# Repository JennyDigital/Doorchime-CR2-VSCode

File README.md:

# I Now Have a Website for this Project!

[https://jennys-stm32-dsp-audio-engine.netlify.app/](https://jennys-stm32-dsp-audio-engine.netlify.app/)

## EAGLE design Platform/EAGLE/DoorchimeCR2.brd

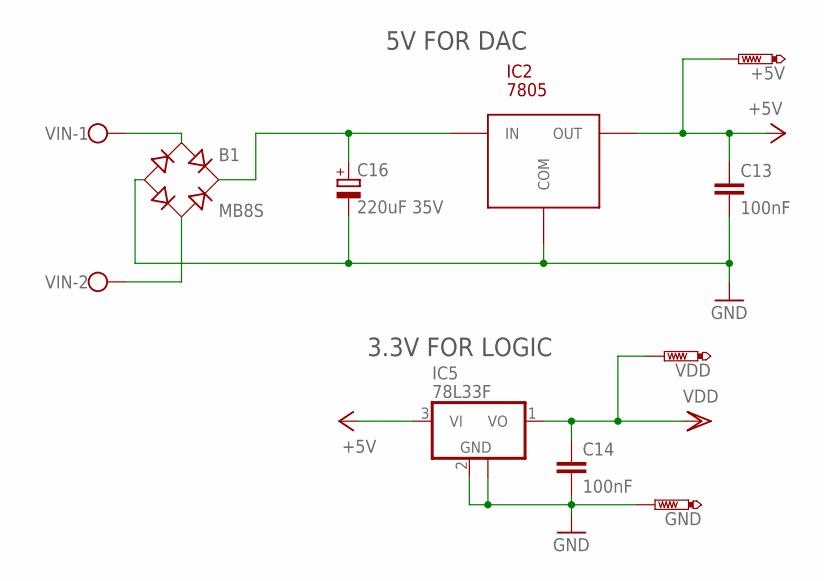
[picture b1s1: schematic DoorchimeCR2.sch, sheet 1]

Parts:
+5V: PTR1TP15R; TP15R
B1: MB8S; SOIC-4
C13, C14: 100nF; C0603
C16: 220uF 35V; 153CLV-0807
GND: PTR1TP15R; TP15R
IC2: 7805; D2PAK
IC5: 78L33F; SOT89
VDD: PTR1TP15R; TP15R
VIN: W237-102

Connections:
+5V: +5V.TP, C13.1, IC2.OUT, IC5.3 (VI); also elsewhere on the board
GND: B1.-, C13.2, C14.2, C16.-, GND.TP, IC2.COM, IC5.2 (GND), IC5.2@1 (GND); also elsewhere on the board
VDD: C14.1, IC5.1 (VO), VDD.TP; also elsewhere on the board
VIN1: B1.~1 (AC1), VIN.1
VIN2: B1.~2 (AC2), VIN.2
VIN+: B1.+, C16.+, IC2.IN

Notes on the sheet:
5V FOR DAC
3.3V FOR LOGIC

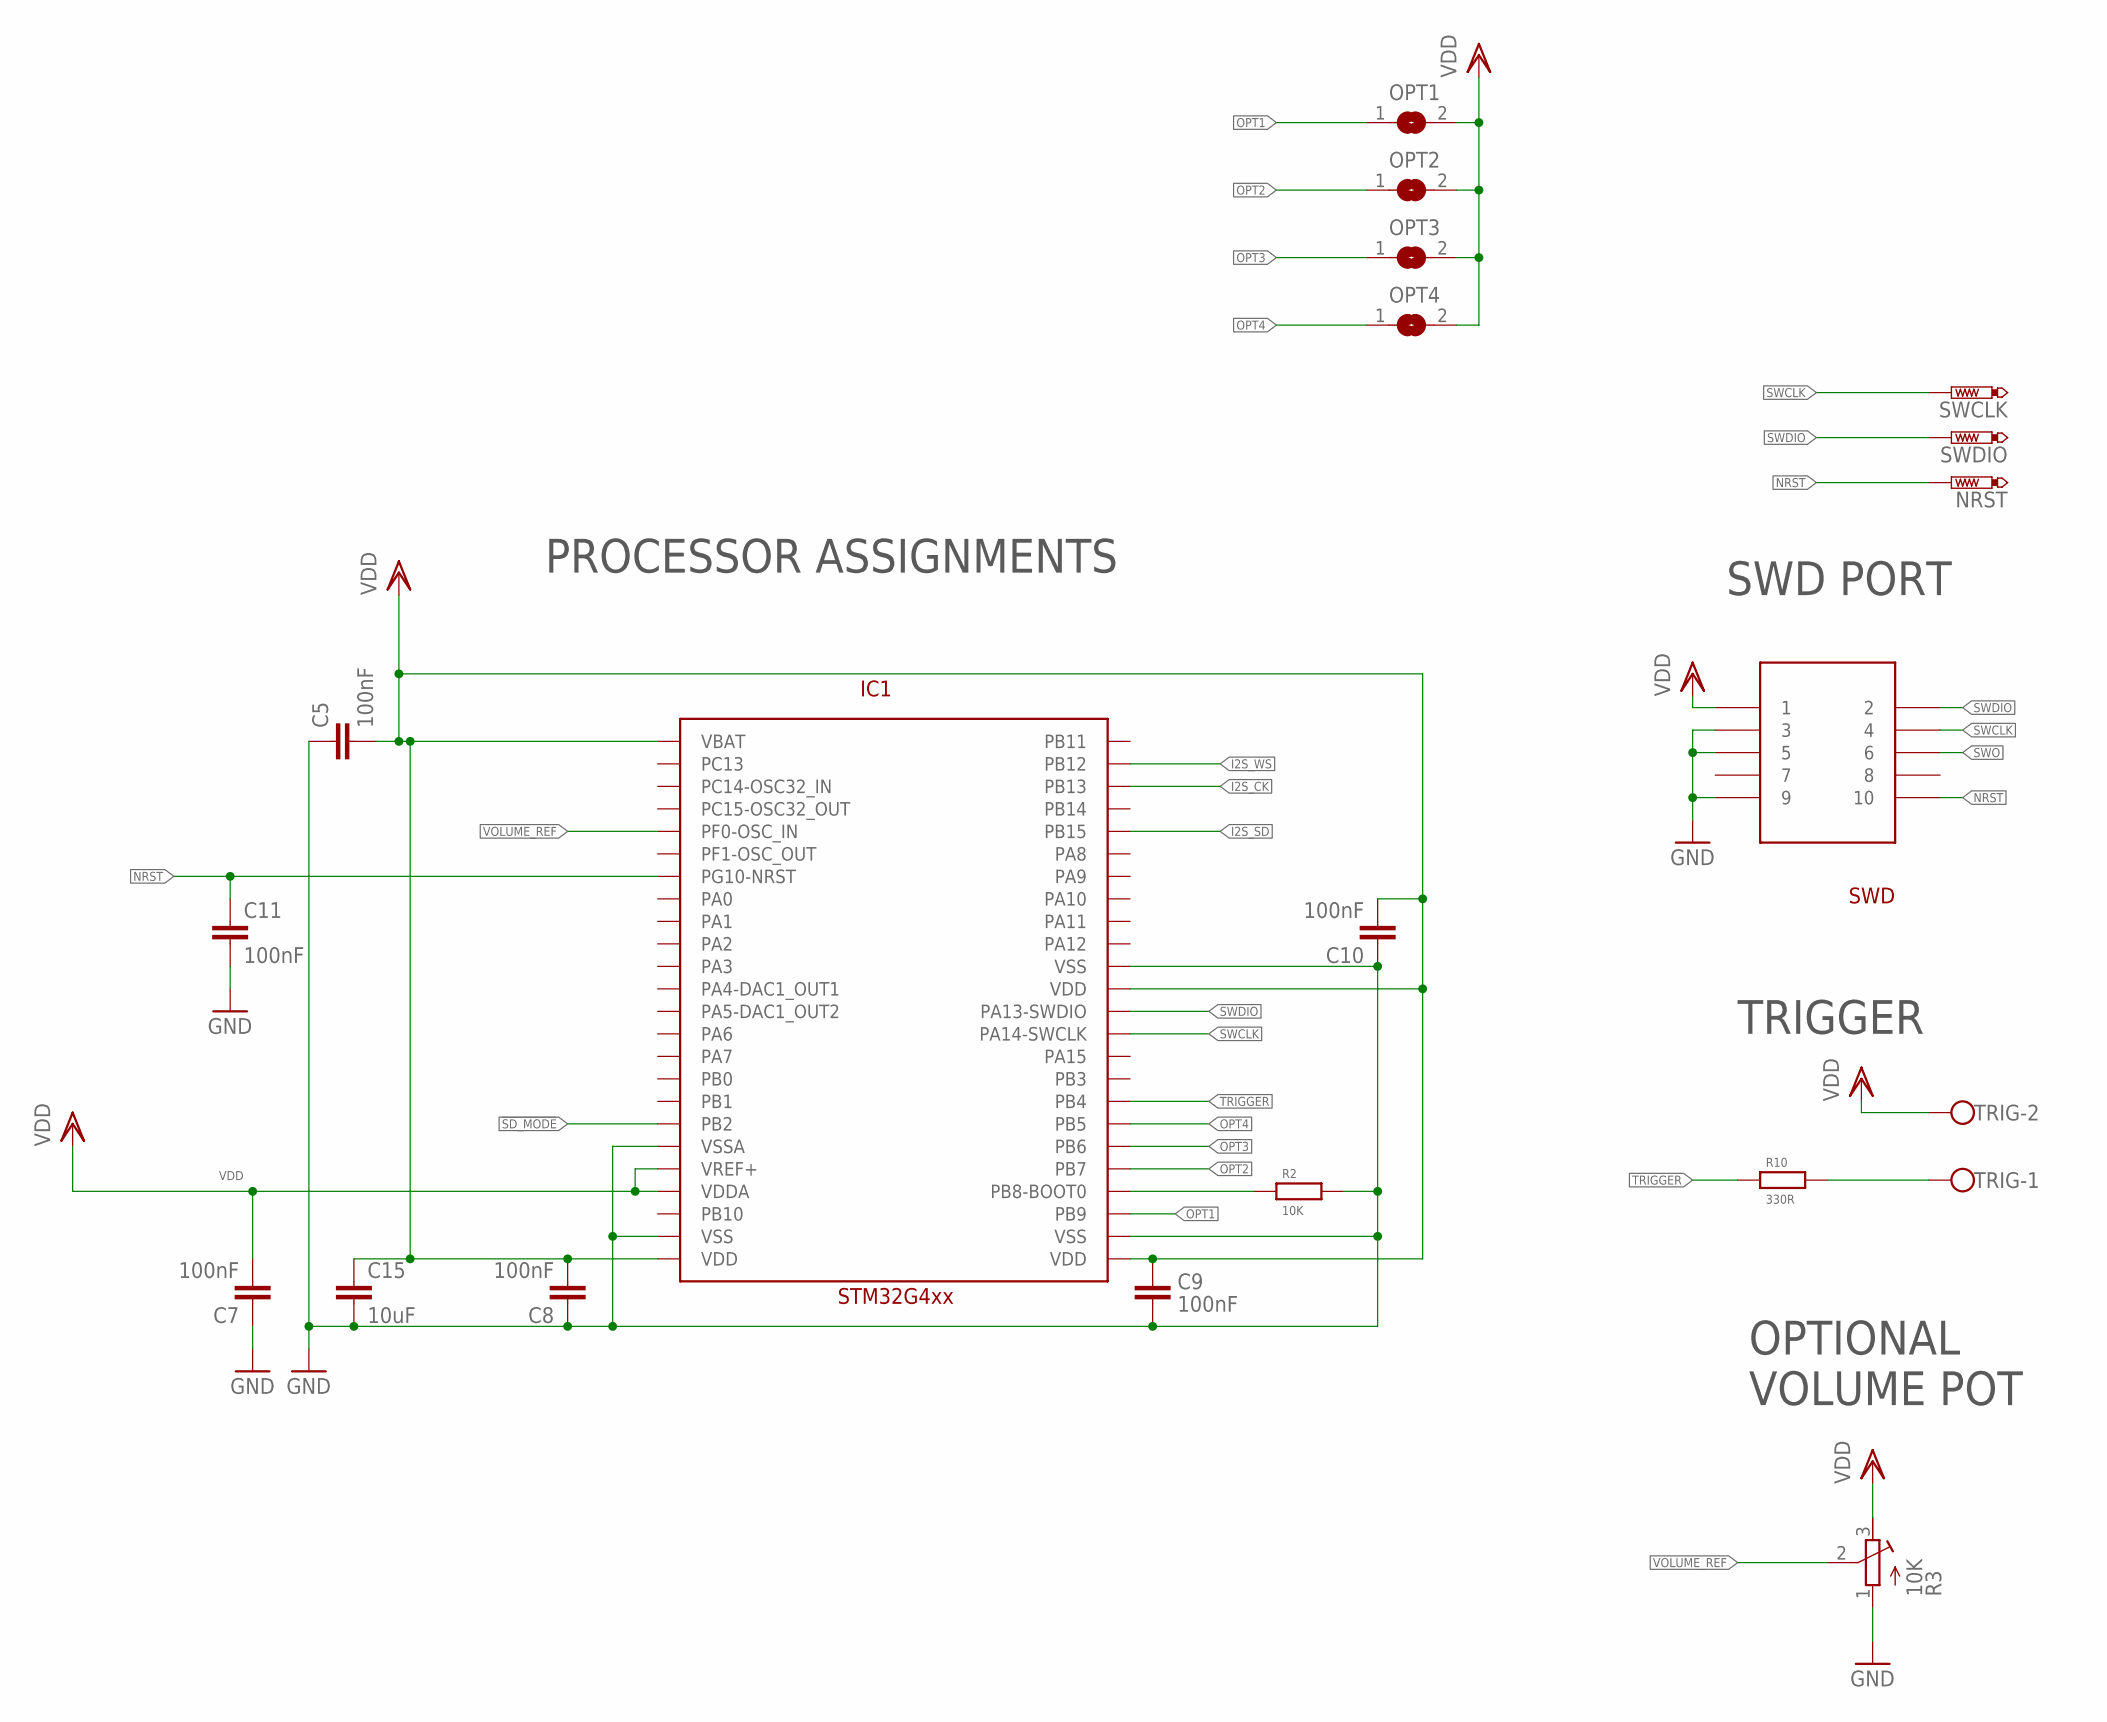
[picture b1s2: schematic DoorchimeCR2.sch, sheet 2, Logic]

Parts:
C5, C7, C8, C9, C10, C11: 100nF; C0603
C15: 10uF; C0603
IC1: STM32G4xx; TQFP48
NRST: PTR1TP15R; TP15R
OPT1, OPT2, OPT3, OPT4: SJ
R2: 10K; R0603
R3: 10K; RTRIM3339P
R10: 330R; R0603
SWCLK: PTR1TP15R; TP15R
SWD: FTSH-105-01; FTSH-105-01-XXX-DV-K
SWDIO: PTR1TP15R; TP15R
TRIG: W237-102

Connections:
!SD_MODE: IC1.PB2; also elsewhere on the board
BOOT0: IC1.PB8-BOOT0, R2.1
GND: C5.1, C7.1, C8.1, C9.1, C10.1, C11.2, C15.2, IC1.VSS@23 (VSS), IC1.VSS@35 (VSS), IC1.VSS@47 (VSS), IC1.VSSA, R2.2, R3.1 (E), SWD.3, SWD.5, SWD.9; also elsewhere on the board
I2S_CK: IC1.PB13; also elsewhere on the board
I2S_SD: IC1.PB15; also elsewhere on the board
I2S_WS: IC1.PB12; also elsewhere on the board
NRST: C11.1, IC1.PG10-NRST, NRST.TP, SWD.10
OPT1: IC1.PB9, OPT1.1
OPT2: IC1.PB7, OPT2.1
OPT3: IC1.PB6, OPT3.1
OPT4: IC1.PB5, OPT4.1
SWCLK: IC1.PA14-SWCLK, SWCLK.TP, SWD.4
SWDIO: IC1.PA13-SWDIO, SWD.2, SWDIO.TP
SWO: SWD.6
TRIG1: R10.2, TRIG.1
TRIGGER: IC1.PB4, R10.1
VDD: C5.2, C7.2, C8.2, C9.2, C10.2, C15.1, IC1.VBAT, IC1.VDD@24 (VDD), IC1.VDD@36 (VDD), IC1.VDD@48 (VDD), IC1.VDDA, IC1.VREF+, OPT1.2, OPT2.2, OPT3.2, OPT4.2, R3.3 (A), SWD.1, TRIG.2; also elsewhere on the board
VOLUME_REF: IC1.PF0-OSC_IN, R3.2 (S)

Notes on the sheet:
PROCESSOR ASSIGNMENTS
TRIGGER
SWD PORT
OPTIONAL VOLUME POT

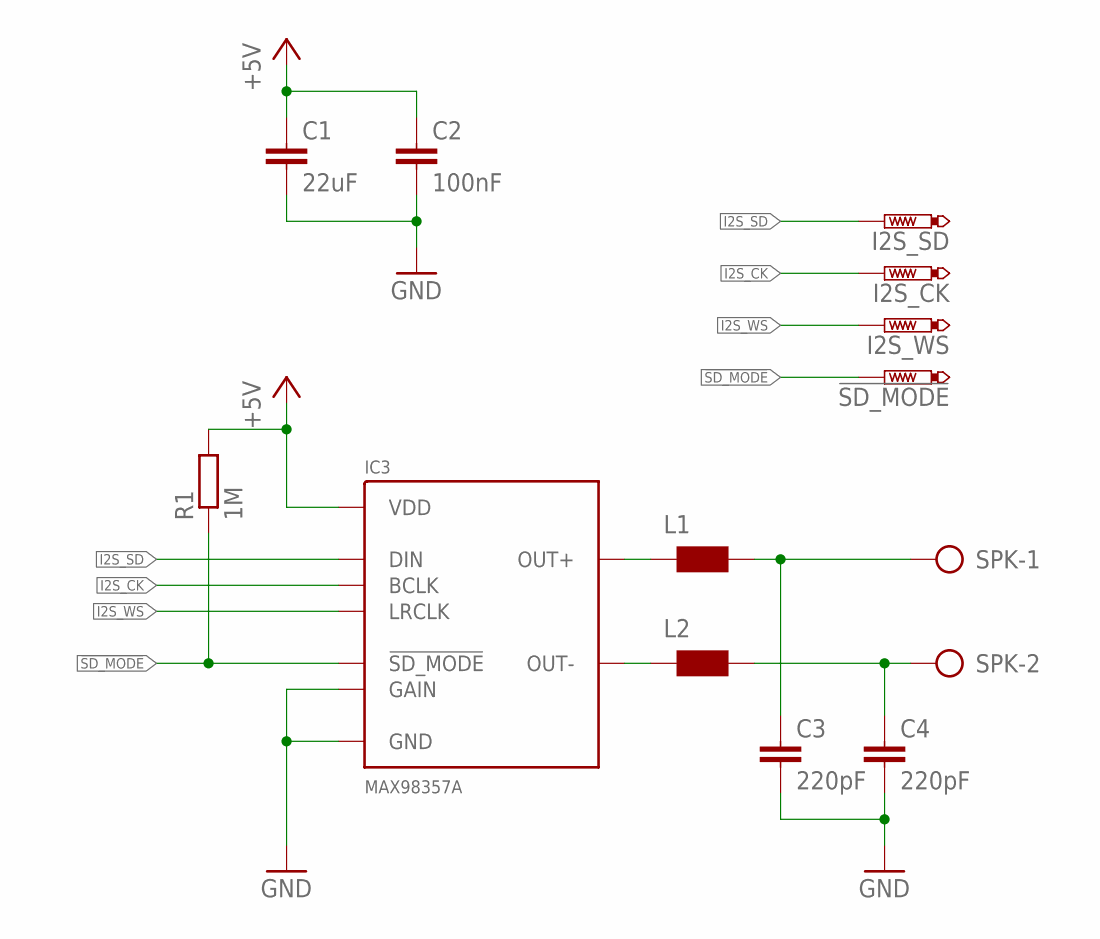
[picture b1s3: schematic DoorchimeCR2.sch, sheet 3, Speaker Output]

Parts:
!SD_MODE: PTR1TP15R; TP15R
C1: 22uF; C0603
C2: 100nF; C0603
C3, C4: 220pF; C0603
I2S_CK, I2S_SD, I2S_WS: PTR1TP15R; TP15R
IC3: MAX98357A; TQFN-16
L1, L2: WE-CBF_0603; 0603
R1: 1M; R0603
SPK: W237-102

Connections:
!SD_MODE: !SD_MODE.TP, IC3.P$4 (!SD_MODE), R1.1; also elsewhere on the board
+5V: C1.1, C2.1, IC3.P$7 (VDD), IC3.P$8 (VDD), R1.2; also elsewhere on the board
GND: C1.2, C2.2, C3.2, C4.2, IC3.P$2 (GAIN), IC3.P$3 (GND), IC3.P$11 (GND), IC3.P$15 (GND), IC3.P$EP (GND); also elsewhere on the board
I2S_CK: I2S_CK.TP, IC3.P$16 (BCLK); also elsewhere on the board
I2S_SD: I2S_SD.TP, IC3.P$1 (DIN); also elsewhere on the board
I2S_WS: I2S_WS.TP, IC3.P$14 (LRCLK); also elsewhere on the board
unnamed: IC3.P$9 (OUT+), L1.1
unnamed: IC3.P$10 (OUT-), L2.1
unnamed: C4.1, L2.2, SPK.2
unnamed: C3.1, L1.2, SPK.1

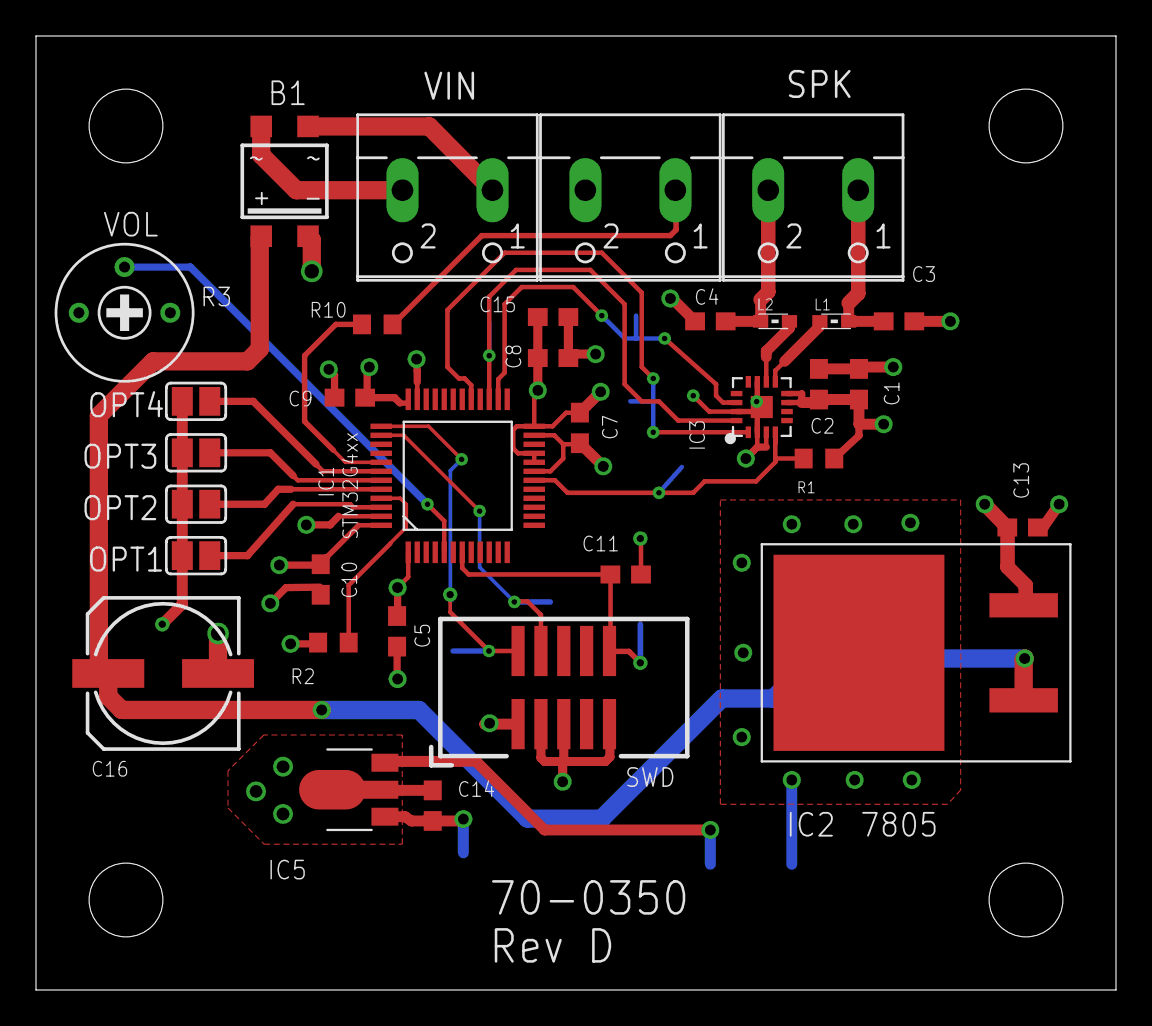
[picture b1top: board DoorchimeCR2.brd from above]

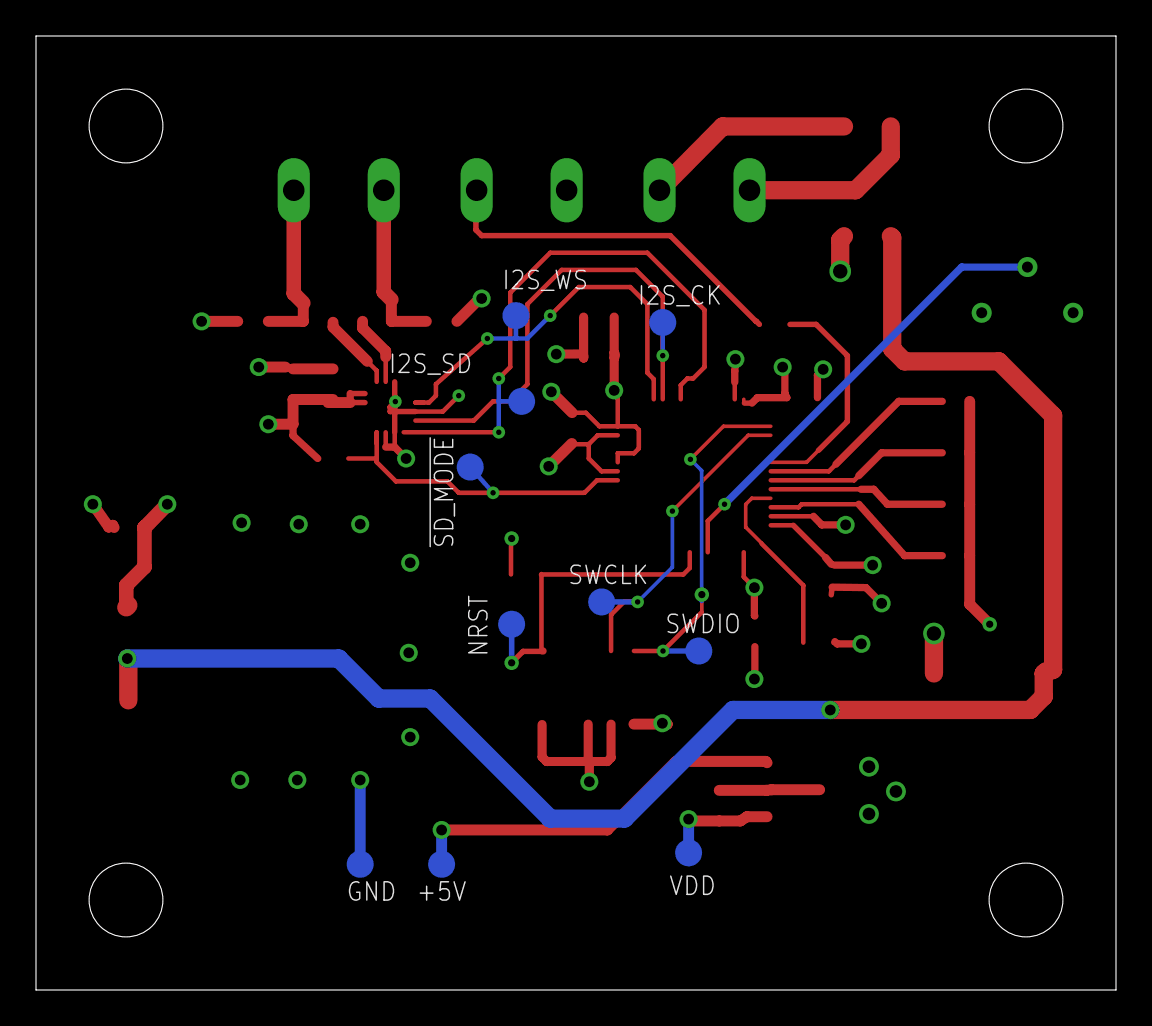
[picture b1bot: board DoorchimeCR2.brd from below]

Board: 4 copper layers, 60.0 x 53.0 mm, 43 parts (10 on the bottom side), 25 nets.

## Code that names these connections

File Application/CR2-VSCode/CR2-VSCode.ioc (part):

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Mcu.Name=STM32G474C(B-C-E)Tx
Mcu.Package=LQFP48
Mcu.UserName=STM32G474CETx
PA13.Mode=Serial_Wire
PA13.Signal=SYS_JTMS-SWDIO
PA14.Mode=Serial_Wire
PA14.Signal=SYS_JTCK-SWCLK
PB12.GPIOParameters=GPIO_Speed
PB12.GPIO_Speed=GPIO_SPEED_FREQ_MEDIUM
PB12.Mode=Half_Duplex_Master
PB12.Signal=I2S2_WS
PB13.GPIOParameters=GPIO_Speed
PB13.GPIO_Speed=GPIO_SPEED_FREQ_MEDIUM
PB13.Mode=Half_Duplex_Master
PB13.Signal=I2S2_CK
PB15.GPIOParameters=GPIO_Speed
PB15.GPIO_Speed=GPIO_SPEED_FREQ_MEDIUM
PB15.Mode=Half_Duplex_Master
PB15.Signal=I2S2_SD
PB2.GPIOParameters=GPIO_PuPd,GPIO_Label,GPIO_ModeDefaultOutputPP
PB2.GPIO_Label=NSD_MODE
PB2.GPIO_ModeDefaultOutputPP=GPIO_MODE_OUTPUT_OD
PB2.GPIO_PuPd=GPIO_NOPULL
PB2.Signal=GPIO_Output
PB4.GPIOParameters=GPIO_PuPd,GPIO_Label
PB4.GPIO_Label=TRIGGER
PB4.GPIO_PuPd=GPIO_PULLDOWN
PB4.Signal=GPIO_Input
PB5.GPIOParameters=GPIO_PuPd,GPIO_Label
PB5.GPIO_Label=OPT4
PB5.GPIO_PuPd=GPIO_PULLDOWN
PB5.Signal=GPIO_Input
PB6.GPIOParameters=GPIO_PuPd,GPIO_Label
PB6.GPIO_Label=OPT3
PB6.GPIO_PuPd=GPIO_PULLDOWN
PB6.Signal=GPIO_Input
PB7.GPIOParameters=GPIO_PuPd,GPIO_Label
PB7.GPIO_Label=OPT2
PB7.GPIO_PuPd=GPIO_PULLDOWN
PB7.Signal=GPIO_Input
PB9.GPIOParameters=GPIO_PuPd,GPIO_Label
PB9.GPIO_Label=OPT1
PB9.GPIO_PuPd=GPIO_PULLDOWN
PB9.Signal=GPIO_Input
RCC.HSE_VALUE=8000000
RCC.SYSCLKFreq_VALUE=96000000
RCC.SYSCLKSource=RCC_SYSCLKSOURCE_PLLCLK
board=custom

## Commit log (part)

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2025-12-20 Added all project files
2025-12-21 Tidied up comments FIX: Fixed a bug in the volume control I'd accidentally introducedd
2025-12-22 Just a aesthetic update
2025-12-24 Added some nice new sounds
2025-12-27 doorchime now killbill11k
2026-01-17 FIXUP: Change error handling to shutdown handling in audio playback TIDYUP: Remove redundant null pointer checks in audio chunk copying functions TIDYUP: Restructure code for better readability in au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
2026-01-19 fixup: adjust end-of-sample checks for pointer types in audio playback code fixup: removed unneccesary commented out code in main.c fixup: removed inappropriate pb_state assignment in TX complete cal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
2026-01-19 FIX: Graceful handling of end-of-sample in audio playback FIX: Corrected typo in volume reading function comment
2026-01-20 FEATURE: Enable EXTI interrupt callbacks and save power by entering sleep mode.
2026-01-21 Improved trigger handling with timout to sleep mode.
2026-01-22 Added a new sound dalby_tritone16b16
2026-01-22 Still working to find a non-popping way to stop playback.
2026-01-23 Added fade-out functionality to audio playback to prevent popping sound at the end of playback. Implemented a function to shut down audio playback gracefully. Adjusted system clock configuration for 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
2026-01-23 FEATURE: Implement a DC blocking filter to remove DC offset from audio samples, improving sound quality.
2026-01-23 Minor tweak to improve code readability in main.c
2026-01-23 FIXED: Added back HAL_I2S_DMAStop call in
2026-01-23 FIX: Fade effect not working properly in certain conditions
2026-01-24 Moved the filter chain to it's own function for clarity. Removed the need for a cast when calling PlaySample by changing the parameter type.
2026-01-24 Added tasks
2026-01-24 Somewhere, I have no recollection, Code appeared in MX_GPIO_Init function that broke the build. It's been removed.
2026-01-24 Build system changes to improve compile times and add new toolchain support.
2026-01-24 Modularity Improvements to Audio Engine
2026-01-24 Adjusted volume reading logic so that we only call the ReadVolume function once per buffer fill, improving efficiency and readability.
2026-01-24 Altered the cutoff frequencies of the low-pass filters for 16-bit audio samples by changing the alpha coefficients in the audio_engine.h file. Updated the visualize_filters_enhanced.py script to refl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
2026-01-24 Add manual for audio_engine.h and generate filter report PDF script Remove AudioEngine_Init declaration from audio_engine.h
2026-01-25 Updated documentation and enhanced filter settings for improved audio quality. Updated graphs to reflect new filter configurations.
2026-01-25 FIX: Warmup documentation and adjust LPF levels
2026-01-25 Added a very nice pdf manual.
2026-01-25 Air lifting and brightening effect added to audio engine. Documentation updated accordingly. Added a new sound header and raw file for testing.
2026-01-25 Updated AUDIO_ENGINE_MANUAL.md and Audio_Engine_Manual.pdf to reflect changes to air effect filter gain and presets.
2026-01-25 Updates to REAME.md.
2026-01-25 Restructured documentation to live in Docs.
2026-01-26 FIXED: Pause and resume playback now fades out and in smoothly. FEATURE: Added functions to set and get fade times for fade-in, fade-out, and pause fade.
2026-01-26 Consolidated dma buffer handling for clearer code and improved memory usage.
2026-01-27 Updated documentation and increased biquad filter performance in audio engine.
2026-01-28 Added calculated delay for shutdown sequence to complete before stopping audio playback.
2026-01-28 Added firm low-pass filter option to PlaySample function call.
2026-01-28 Addeed further MIT Liccense header to main.c
2026-01-30 Uodated project to include latest HAL drivers and configurations. Added support for TIMER and ADC peripherals.
2026-01-30 Quick amendment to the order or restarting the ADC and TIM7 after waking from sleep mode.
2026-01-30 Fixed audio distortion issue in audio_engine.c
2026-01-30 Moved ShutDownAudio declaration to audio_engine.h and audio_engine.c
2026-01-31 Final aesthetic adjustments made to code style.
2026-01-31 Improved low-pass filter function and added soft noise gate in audio engine.
2026-01-31 Feature: Added getters and setters for audio engine configuration. There are still some to more to add.
2026-01-31 Moved some functions in static for reducing scope.
2026-02-01 FIX: Volume Input and Trigger Optimization NEW SOUND HEADER: We have a dalby_tritoneJan26 sound header and raw file added.
2026-02-01 Updated the audio emgine documentation and main header file.
2026-02-01 Added null check before using audio engine pointer. Updated BUG_REPORT.md to reflect changes in audio engine handling.
2026-02-02 FEATURE: PausePlayback is now non-blocking FIX: Removed DAC de and reinitialization during pause and resume to remove audio glitches
2026-02-03 Special configuration for Dalby Engineering offering.
2026-02-03 Update documentation and add interrupt protection utilities
    - Document pause/resume edge case handling (fade-in and end-of-file fadeout interruptions)
    - Update default pause fadeout duration (1.0 seconds instead of 100 ms)
    - Create interrupt_utils.h with ATOMIC_ENTER/ATOMIC_EXIT macros for atomic operations
    - Convert all spellings to British English (artifact -> artefact)
    - Update main.c to use new atomic operation macros
    - Document proportional scaling and quadratic fade curves in API reference
2026-02-03 Update filter report Air Effect presets to +1/+2/+3 dB
    - Correct presets list and summary text to reflect +1, +2, +3 dB options
    - Regenerate PDF with updated specifications
2026-02-03 Regenerated the manual
2026-02-03 Further fixes to AUDIO_ENGINE_FLOWCHART.md
2026-02-03 Hopefully the last fixes to AUDIO_ENGINE_FLOWCHART.md
2026-02-03 FIX: Added data and instruction barriers in interrupt utils.h to ensure proper ordering of operations when enabling and disabling interrupts.
2026-02-04 Improved volume reading and response handling. We now use a 16-bit volume range derived from a 12-bit ADC input, ensuring finer control over volume levels. The volume response can be toggled between 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
2026-02-04 FIX: Removed redundant GetStopStatus() function and replaced with GetPlaybackState().
2026-02-05 FEATURE: Added weak callback for end of sample playback.
2026-02-05 Improved contrast in the flowcharts.
2026-02-06 Added macro to fill audio buffer with midpoint value for silence, and used it in two places in audio_engine.c where the buffer needs to be filled with silence.
2026-02-06 We now fill the whole buffer with midpoint values when ending, this is because sometimes we end up playing a half chunk of audio after the fadeout has completed, which results in a small amount of no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
2026-02-06 Moved documentation to a better location.
2026-02-07 REFACTOR: Moved the macros STOP_IMMEDIATE and END_PLAYBACK_CLEANUP tO audio_engine.c as inline functions. This change was made to improve code maintainablilith and ease debugging.
2026-02-07 Moved helper functions RecalculateFadeSamples, EndPlaybackCleanup and StopImmediate to near the DMA callback function they're used in.
2026-02-07 FIX: ShutDownAudio now immediately halts DMA and resets state, instead of waiting for the buffer to drain. This is because StopPlayback does this asynchronously, and wse don't need two functions that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
2026-02-07 Updated pb8, pb16, pb8_end and pb16_end pointer names to end in _ptr for consistency and clarity.
2026-02-07 Updated documentation to reflect changes in audio engine API and fix inconsistencies.
2026-02-07 Removed mention of the non-existent CHANGELOG.md file.
2026-02-07 Minor corrections to documentation and code comments.
2026-02-07 Aesthetic changes to the code for better readability. No functional changes were made.
2026-02-07 Slighgt code tidying and refactoring for better readability and maintainability. No functional changes intended.
2026-02-08 Docuementation updates and license addition
2026-02-08 Removed #include's from main.c for files that have been deleted.
2026-02-09 FEATURE:- Added some new sound headers. FEATURE:- Added master enable flags for entire filter chains in audio_engine.c and audio_engine.h. FEATURE:- Updated main.c to set default states for new filte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
2026-02-11 CLEANUP: Removed redundant typedef and minor adjujstment to formatting.
2026-02-15 FIX:- Removed redundant code in audio_engine.c
2026-02-20 FIX: Double bounds check removed from ApplyLowPassFilter16Bit() in audio_engine.c Minimum volume clamp now defined by VOLUME_MIN_CLAMP in main.h.
2026-02-21 NEW SOUND: didgeridoo
2026-02-28 pb_state variable was changed from uint8_t to PB_StatusTypeDef enum for better readability and type safety. The GetPlaybackState and SetPlaybackState functions were updated accordingly to use the new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
2026-03-01 FIX: Cleaned up pause/resume logic and added comments. Edge case handling for invalid state transitions. Updated main.c to demonstrate pause/resume functionality with appropriate delays.
2026-03-01 Volume is now processed per frame rather than per chunk, which allows for more accurate volume control and better performance. Additionally, the audio engine now supports dynamic volume changes, allo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
2026-03-08 FIX: Ensure DAC is switched off after playback ends if power control is enabled, there were edge cases where it remained on after playback ended, this change adds a check to ensure it is switched off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
2026-03-08 Added a nice logo and updated the documentation. Portability guide and some minor code tweaks to prevent integer overflow in the biquad filter when processing 16-bit samples with certain configuratio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
2026-03-08 Update: links now updated.
2026-03-08 FIX: Markdown should now be rendered correctly on the website. The issue was caused by the fact that the markdown files were being served with a .md extension, which caused the browser to treat them 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
2026-03-08 FIX: Markdown viewing of web-hosted docs and license file links did not work. Updated links to point to docs-viewer.html with appropriate query parameters for both the main index and the docs page. A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
2026-03-10 FEATURE: Add secret door sound effect. FEATURE: Remove dependency on SysTick for HAL_Delay in audio engine. This is because it forces SysTick to have a higher priority than the audio engine's DMA int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
2026-03-10 Updated website documentation and styles.
2026-03-12 Fix formatting of README.md.
2026-03-19 FIX: Update documentation to reflect the new API changes and features. FEATURE: Add new API functions to control filter chain enablement for 16-bit and 8-bit modes. FEATURE: Add playback progress tra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
2026-03-19 Fix unnecessary capitalization in 'Website' in README.md

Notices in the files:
parts and their libraries:
SparkFun-IC-Amplifiers: Licensing: Creative Commons ShareAlike 4.0 International - https://creativecommons.org/licenses/by-sa/4.0
wuerth-elektronik: Copyright: Würth Elektronik eiSos
